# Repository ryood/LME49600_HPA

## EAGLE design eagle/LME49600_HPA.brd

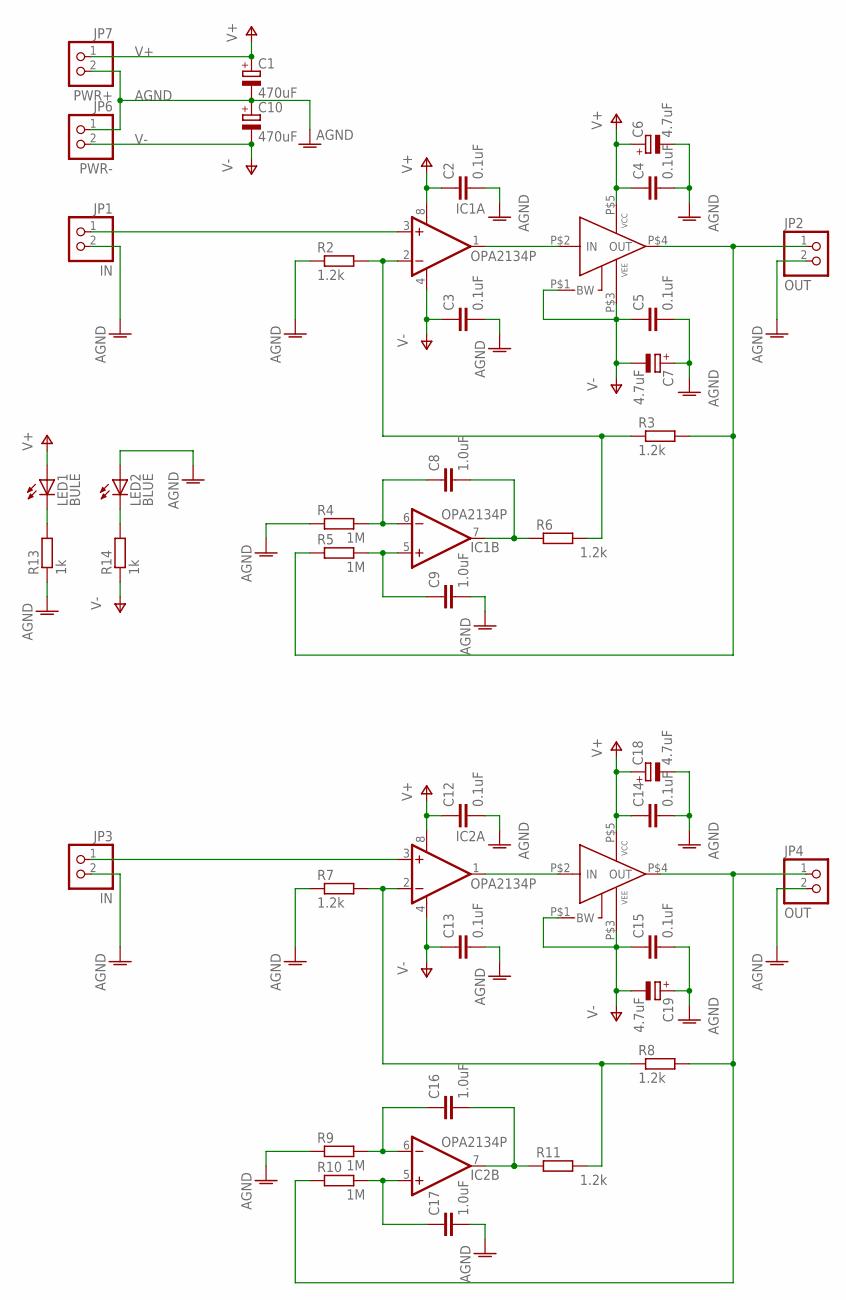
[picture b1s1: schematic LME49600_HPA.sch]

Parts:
C1, C10: 470uF; E7,5-16
C2, C3, C12, C13: 0.1uF; C075-042X103
C4, C5, C14, C15: 0.1uF; C050H075X075
C6, C7, C18, C19: 4.7uF; E2-4
C8, C9, C16, C17: 1.0uF; C050-050X075
IC1, IC2: OPA2134P; DIL08
JP1, JP3: IN; 1X02
JP2, JP4: OUT; 1X02
JP6: PWR-; 1X02
JP7: PWR+; 1X02
LED1: BULE; LED3MM
LED2: BLUE; LED3MM
R2, R3, R6, R7, R8, R11: 1.2k; 0207/7
R4, R5, R9, R10: 1M; 0207/7
R13, R14: 1k; 0207/7
U$1, U$2: LME49600-BRD2; SIP5-9

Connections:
AGND: C1.-, C2.2, C3.2, C4.2, C5.2, C6.-, C7.+, C9.2, C10.+, C12.2, C13.2, C14.2, C15.2, C17.2, C18.-, C19.+, JP1.2, JP2.2, JP3.2, JP4.2, JP6.1, JP7.2, LED2.A, R2.1, R4.1, R7.1, R9.1, R13.1
unnamed: IC1.3 (+IN), JP1.1
unnamed: IC1.2 (-IN), R2.2, R3.1, R6.2
unnamed: IC2.2 (-IN), R7.2, R8.1, R11.2
unnamed: IC2.1 (OUT), U$2.P$2 (IN)
unnamed: C8.1, IC1.6 (-IN), R4.2
unnamed: IC1.1 (OUT), U$1.P$2 (IN)
unnamed: C9.1, IC1.5 (+IN), R5.2
unnamed: C16.1, IC2.6 (-IN), R9.2
unnamed: C17.1, IC2.5 (+IN), R10.2
unnamed: C8.2, IC1.7 (OUT), R6.1
unnamed: C16.2, IC2.7 (OUT), R11.1
unnamed: JP4.1, R8.2, R10.1, U$2.P$4 (OUT)
unnamed: JP2.1, R3.2, R5.1, U$1.P$4 (OUT)
unnamed: IC2.3 (+IN), JP3.1
unnamed: LED1.K (C), R13.2
unnamed: LED2.K (C), R14.2
V+: C1.+, C2.1, C4.1, C6.+, C12.1, C14.1, C18.+, IC1.8 (V+), IC2.8 (V+), JP7.1, LED1.A, U$1.P$5 (VCC), U$2.P$5 (VCC)
V-: C3.1, C5.1, C7.-, C10.-, C13.1, C15.1, C19.-, IC1.4 (V-), IC2.4 (V-), JP6.2, R14.1, U$1.P$1 (BW), U$1.P$3 (VEE), U$2.P$1 (BW), U$2.P$3 (VEE)

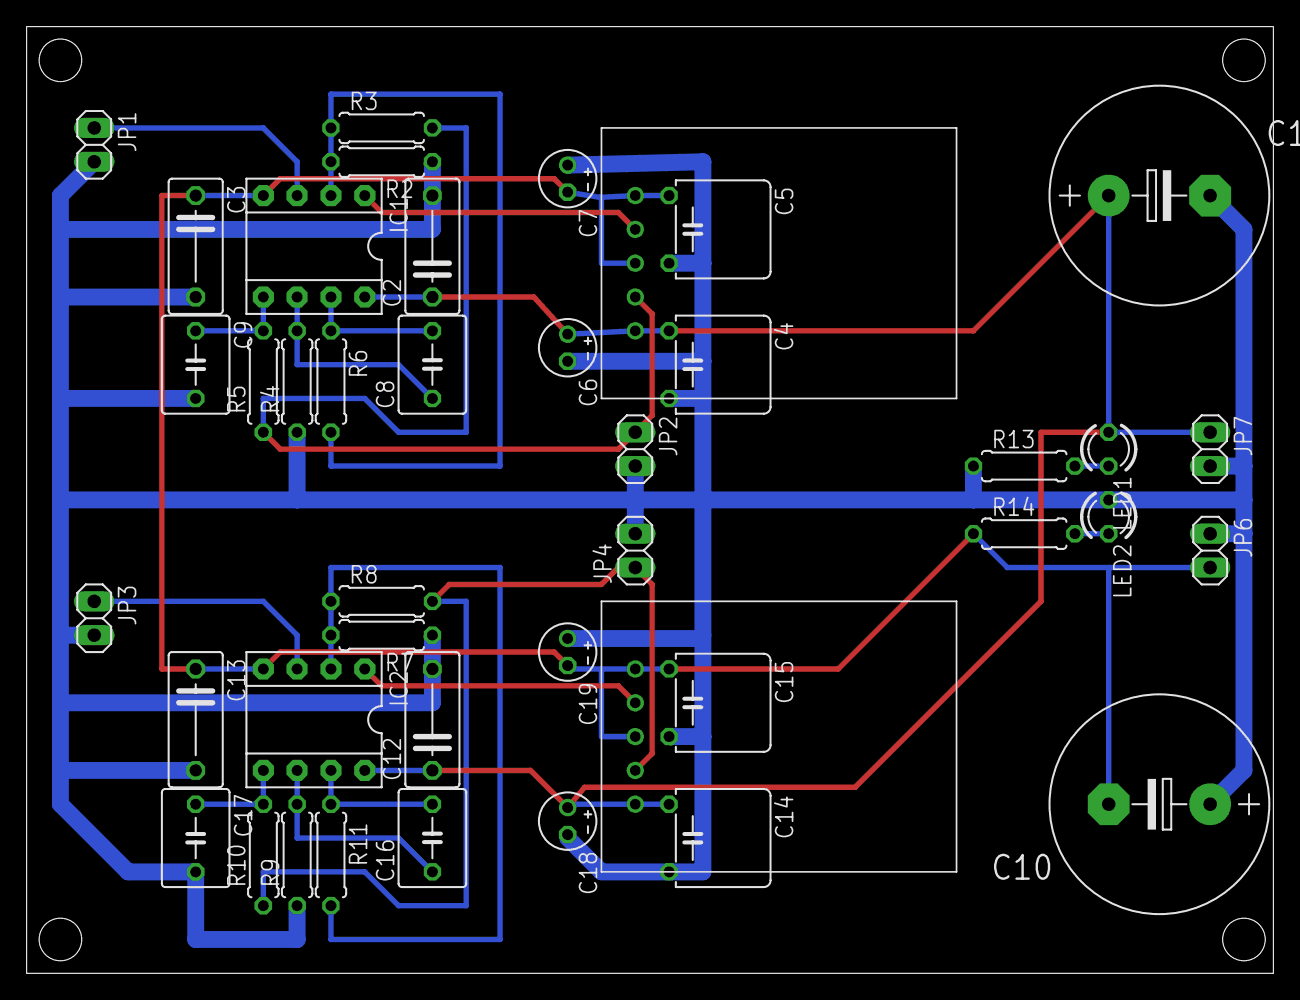
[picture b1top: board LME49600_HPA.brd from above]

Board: 2 copper layers, 93.7 x 71.1 mm, 42 parts (0 on the bottom side), 19 nets.

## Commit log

2016-07-18 Add: Power Supply
2016-07-18 bug fix
2016-08-07 Change board size of LME49600
2016-08-17 Update: Board Design
2016-08-17 Change: Board size of LME49600
2016-08-17 Add: Pilot LED
2016-09-18 Completed Soldering
2016-09-24 Add: Polycarbonate Case CAD
